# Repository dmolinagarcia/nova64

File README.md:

# noVa64 

**What it is noVa64?**

The noVa64 (With an uppercase V) is a new computer built around the 65816 CPU. Inspired by the age of 8-bit computers, it's envisioned as a alternate-universe succesor to the Commodore 8-bit series of computers. Instead of adquiring the Amiga, could've Commodore created a 16-bit machine around this CPU? The noVa64 is designed and built by a hobbyist (me) who will need to learn pretty much everything on the go.

**What it isn't noVa64?**

It's not a professional or commercially viable product.  It's not meant to be mass produced. It's not a recreation of any pre-existing computer, although it will be inspired by many.

**When will it be ready?**

Hopefully, at some point. That's all I can say.

## Principles

- Not here for the money. This is not meant to be a commercial product
- Hence, no restrictions on parts (Used, obsolete, questionable sources)
- Learn from scratch. No off-the-shelf solution
- Inspiration on others is encouraged though
- Give credit to all sources of information
- Everything will be open sourced, under the GNU v3 License
- Log all the steps
- No deadline. 
- Learn
- Have fun

## Requirements

### Form factor

- Computer should be a laptop, fully portable

### Power

- Single and low voltage. 5v is very obsolete. At least 3.3v, maybe even lower
- Battery powered
- USB-C Charger, allowing for fast charge if possible
- Battery pack reports to the computer. Charge status, capacity, etc
- Computer then display this

### CPU

- Based around a 65816. Real CPU, no FPGA here
- DRAM. Maximum memory at 16MB for the CPU 
- SRAM cache for the main DRAM

### Chipset

- Set of sustaining chips
- FPGA acting as MMU, handling DRAM, with potential for bigger RAM
- IO/TIMER. Could use a 6526 in FPGA maybe. TIMERs need to be driven by independent clock
- RTC. Used to keep time. Can act as TIMERS too for interrupts

### Video

- At least 640x400 (Twice a C64). 256 colors
- FPGA is allowed here
- Built in Laptop Screen
- External monitor an option (mirror, or extend if possible)
- VGA or HDMI for external monitor
- Brightness controlled via software
- Still not sure about dedicated video RAM

### Audio

- Stereo audio and built-in speakers
- FPGA is allowed here too
- External audio an option (Through audio jack, or, if possible HDMI)
- Volumen control through software

### Peripherals

- USB Support for storage, and HID
- Internal keyboard and trackpad are USB
- External ports too

### Storage

- Dual SD. One acting as internal hd, one acting as eternal storage

### Connectivity

- Is TCP/IP Possible? Wifi? Ethernet?

### Boot sequence

- Small ROM to handle booting. Then, SO from "INTERNAL" sd is loaded into meemory

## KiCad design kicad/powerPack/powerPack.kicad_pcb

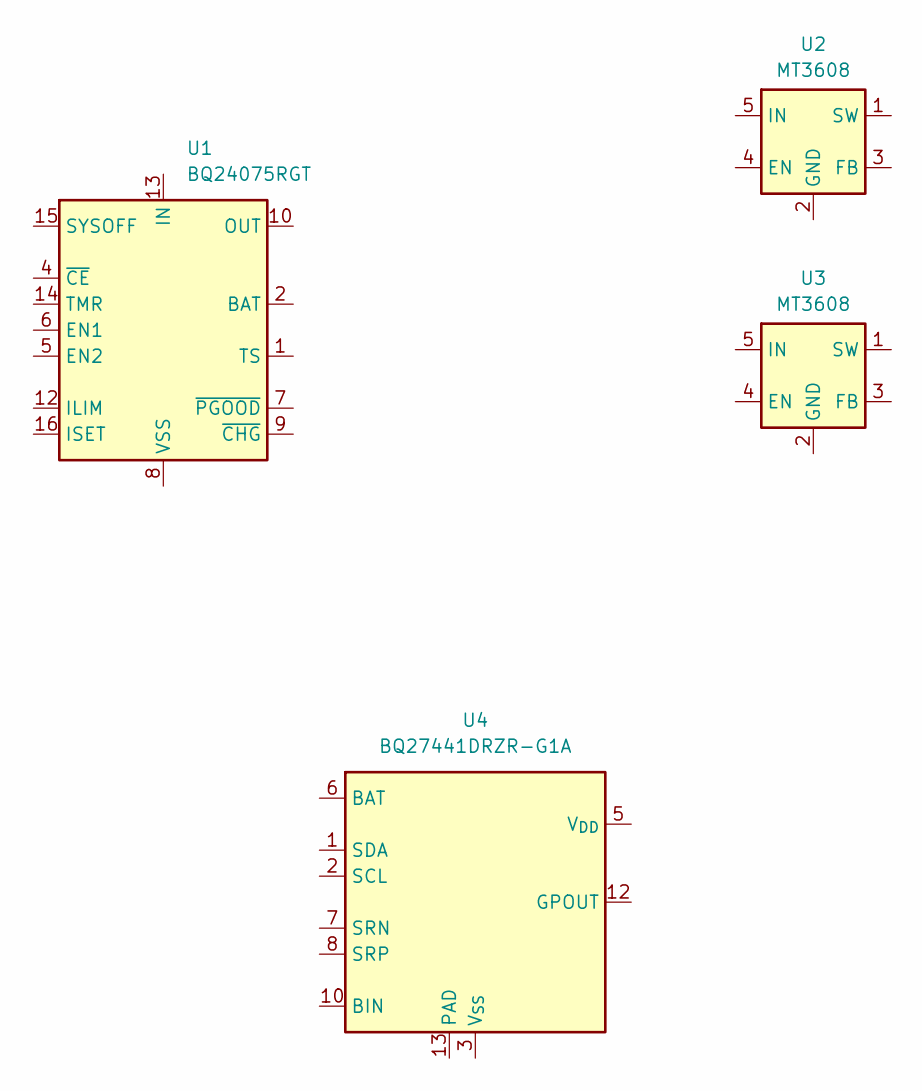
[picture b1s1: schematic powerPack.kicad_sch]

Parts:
U1: BQ24075RGT; VQFN-16-1EP_3x3mm_P0.5mm_EP1.6x1.6mm
U2, U3: MT3608; SOT-23-6
U4: BQ27441DRZR-G1A; Texas_S-PDSO-N12

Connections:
unnamed: U1.2 (BAT), U1.3 (BAT)
unnamed: U1.10 (OUT), U1.11 (OUT)
unnamed: U1.8 (VSS), U1.17 (VSS)

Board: 2 copper layers, 4 parts (0 on the bottom side), 3 nets, no tracks yet.

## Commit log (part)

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2022-12-13 Initial Site setup
2022-12-13 Test Post
2022-12-13 name
2022-12-13 excerpts
2022-12-13 Add header
2022-12-13 clean.
2022-12-13 navigation
2022-12-13 nav2
2022-12-13 Posts
2022-12-14 Testing tags
2022-12-14 Tag page
2022-12-14 categories?
2022-12-14 Categories update
2022-12-14 Category navegation
2022-12-14 Archive Permalink
2022-12-14 archive and references permalink
2022-12-14 Requirements page
2022-12-14 Categories.md
2022-12-14 Categories!
2022-12-14 Mas Categories
2022-12-14 Finally categories
2022-12-14 Ains...
2022-12-14 Clear Menu Bar
2022-12-14 Ains.
2022-12-14 Archive.
2022-12-14 Adding comments to site
2022-12-14 comments
2022-12-14 logos
2022-12-14 Logo in header
2022-12-14 Logo
2022-12-14 Logo again
2022-12-14 Requs
2022-12-14 Title
2022-12-14 Fix header
2022-12-14 Social Links
2022-12-14 Fix Social links
2022-12-14 Category links
2022-12-14 Fix Categories
2022-12-14 Fix Categories again
2022-12-15 Posts moved to drafts
2022-12-15 Footer
2022-12-15 Syntax Highlighting
2022-12-15 Assembly
2022-12-15 highlighter
2022-12-15 6502 asm
2022-12-15 Removed Google+ from sharelinks
2022-12-15 Initial Post and General Category
2022-12-15 Fix Category pages
2022-12-15 First Post
2022-12-15 First post corrections. Added 6502.org into references.
2022-12-15 LICENSE
2022-12-16 Just a Test
2022-12-16 2022-12-16 Post
2022-12-17 Diagram fixed
2022-12-18 Added Andre references
2022-12-19 Added category Memory. Plus one draft
2022-12-19 Draft
2022-12-19 Head
2022-12-20 2022-12-20 Post. Cache added to requirements.
2022-12-20 Trying to fix social URLs
2022-12-20 Trying to fix social links
2022-12-20 og:image
2022-12-20 ogimage
2022-12-20 og:image tags
2022-12-20 Twitter card
2022-12-20 Tidy Head
2022-12-20 Fix head
2022-12-20 OG Image
2022-12-20 delete
2022-12-21 Some V tests
2022-12-21 Updated excerpt
2022-12-21 More verilog
2022-12-21 Verilog
2022-12-22 Cache.v
2022-12-23 Integrated With windows
2022-12-24 Cache and Draft
2022-12-24 Cache
2022-12-31 Cache test
2023-01-05 Power Draft
2023-01-06 Drafting the battery
2023-02-03 Added C
2023-02-05 Let's start with C Code!
2023-02-20 C testing
2023-05-23 Added noVa64 - architecture
2023-05-23 Update noVa64 - architecture
